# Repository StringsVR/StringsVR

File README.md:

# Strings VR

## Vision

### Overview
StringsVR is aimed to make a wireless SteamVR-compatible setup using the Orange Pi 2W, 6dof tracking also supported through cameras on front of Headset.

### Streaming
StringsVR is currently capable of streaming 2k@72hz over a strong wifi connection with 19ms of latency.
**(This will highly depend on your Wi-Fi it is recommended to have your PC connected to ethernet)** 

### Hardware

#### Power PCB

| Components  | Amount |
| ------------- | ------------- |
| 3200mah 18650 | 3x |
| 18650 Holder PCB | 3x |
| TP4056 | 1x |
| MT3086 | 1x |
| 2x1 Arduino Header | 1x |
| SPDT Power Switch | 1x |
| StringsVR Power PCB | 1x |
| MPU9250 | 1x |

#### Misc
| Components  | Amount |
| ------------- | ------------- |
| Orange Pi Zero 2W 2GB | 1x |
| LS055R1SX04 | 1x |
| HDMI Mini to HDMI Micro USB | 1x |
| USB-Micro USB 5V@1A | 1x |
| 50mmX30mm lenses | 1x |

### Progress ##
**V2 currently is out**, Wiki is not finished but is buildable. V2 will be alot easier setup involving controllers aswell asmore compact

### How To Setup & Build
Check The [Wiki](https://github.com/StringsVR/StringsVR/wiki/Getting-Started).

### Trello & Discord
Trello: https://trello.com/b/QIIqky8U (Add Suggestions to suggestions category)
Discord: stringsbutanalt 

# Project is back in development!!

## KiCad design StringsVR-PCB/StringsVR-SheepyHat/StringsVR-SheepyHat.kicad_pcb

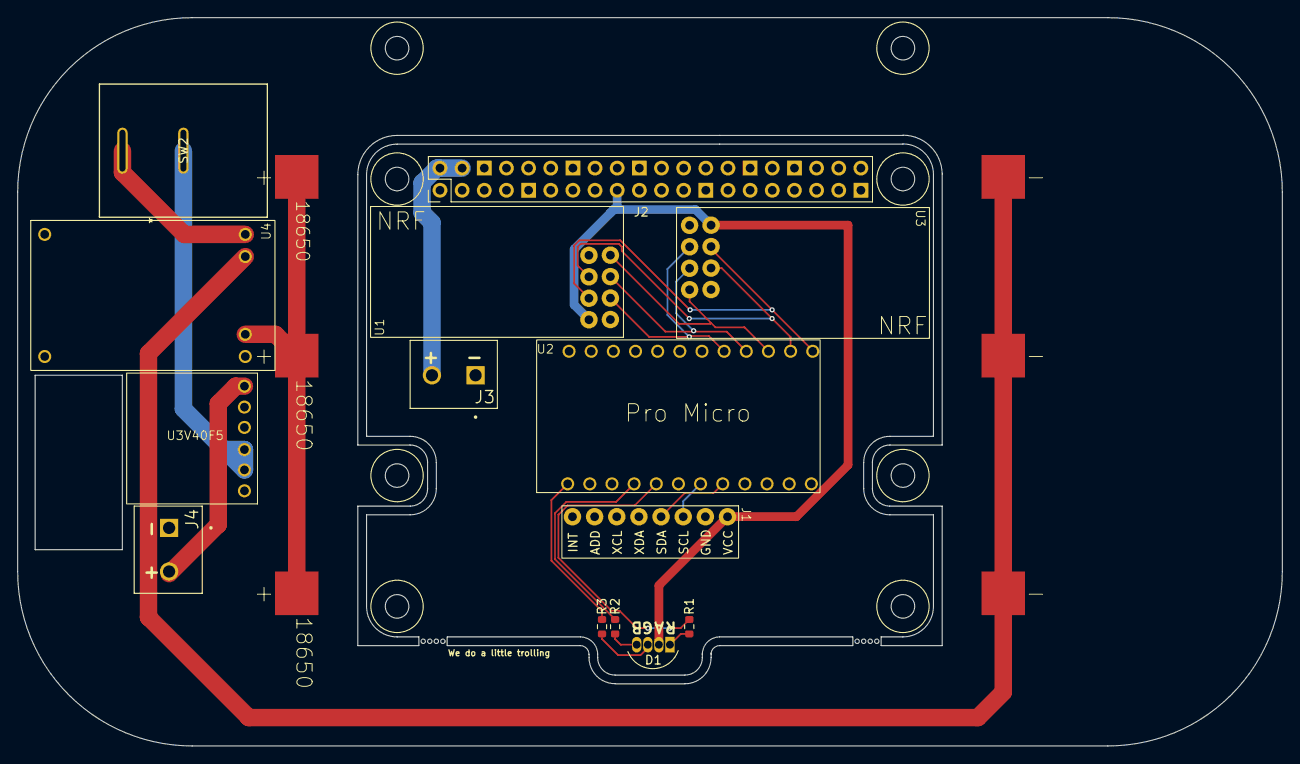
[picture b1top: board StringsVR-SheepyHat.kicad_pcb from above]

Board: 2 copper layers, 145.0 x 83.5 mm, 17 parts (0 on the bottom side), 20 nets.

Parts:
D1: LED_RABG; LED_D5.0mm-4_RGB
J1: MPU6050
J2: Conn_02x20_Odd_Even; Pin_Header_Straight_2x20_Pitch2.54mm
J3, J4: Screw_Terminal_01x02; CUI_TB003-500-P02BE
R1, R2, R3: 220; R_0603_1608Metric
SW2: SRB22A2BBBNN; SW_SRB22A2BBBNN_ZFE
U1, U3: nRF24L01
U2: Pro Micro
U4: TP4056
U5: U3V40F5
U6, U7, U8: 18650SMD

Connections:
5V regulated: J2.2, J2.4, J3.2, J4.2, U5.6 (VOUT)
+3.3V: D1.2 (A), J1.1, J2.17, U1.5 (VCC), U3.5 (VCC)
/B+: U4.4 (B+), U6.1 (b+), U7.1 (b+), U8.1 (b+)
/B-: U4.5 (B-), U6.2 (b-), U7.2 (b-), U8.2 (b-)
CE: U1.2 (CE), U2.20 (Analog), U3.2 (CE)
CSN: U1.6 (CSN), U2.24 (Analog), U3.6 (CSN)
GND: J1.2, J2.6, J2.9, J2.25, J2.30, J2.34, J2.39, J3.1, J4.1, U1.1 (GND), U3.1 (GND), U4.6 (OUT-), U5.4 (GND), U5.5 (GND)
LED_B: R3.2, U2.12 (Analog)
LED_G: R2.2, U2.9 (Analog)
LED_R: R1.2, U2.8 (Analog)
MISO: U1.4 (MISO), U2.22 (MISO), U3.4 (MISO)
MOSI: U1.7 (MOSI), U2.23 (MOSI), U3.7 (MOSI)
unnamed: D1.3 (BK), R3.1
unnamed: D1.4 (GK), R2.1
unnamed: D1.1 (RK), R1.1
unnamed: SW2.2, U5.2 (VIN), U5.3 (VIN)
unnamed: SW2.1, U4.3 (OUT+)
SCK: U1.3 (SCK), U2.21 (SCLK), U3.3 (SCK)
SCL: J1.3, U2.6 (SCL)
SDA: J1.4, U2.5 (SDA)

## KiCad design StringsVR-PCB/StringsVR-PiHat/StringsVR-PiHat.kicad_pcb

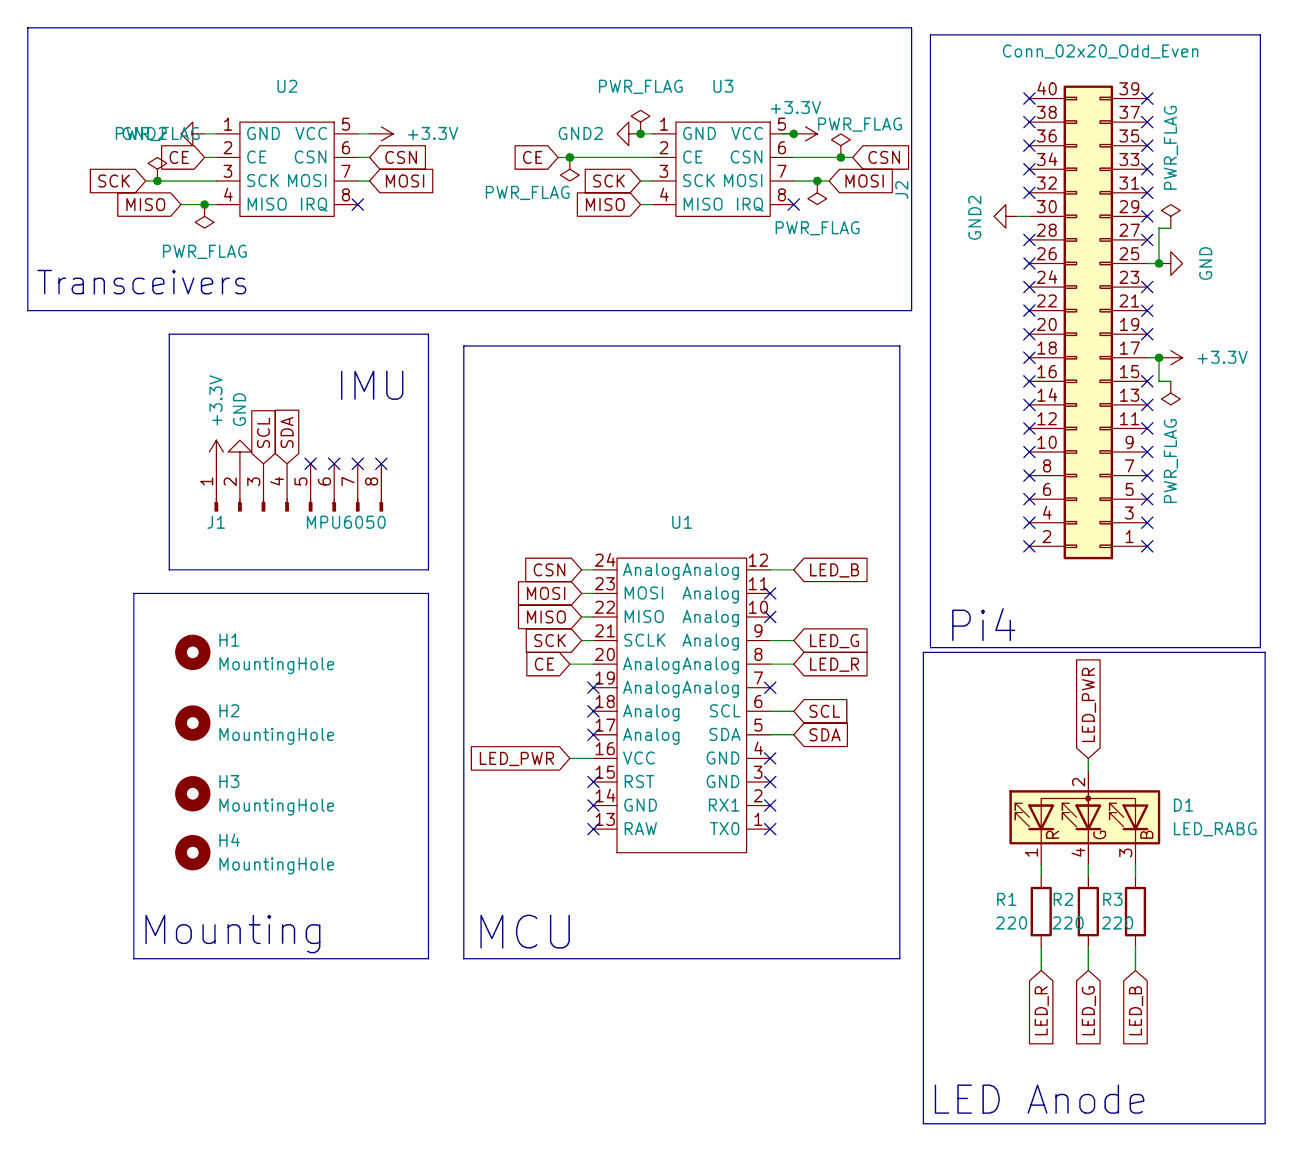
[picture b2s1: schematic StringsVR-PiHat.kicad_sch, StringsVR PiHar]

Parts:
D1: LED_RABG; LED_D5.0mm-4_RGB
H1, H2, H3, H4: MountingHole; MountingHole_2.7mm
J1: MPU6050
J2: Conn_02x20_Odd_Even; Pin_Header_Straight_2x20_Pitch2.54mm
R1, R2, R3: 220; R_0603_1608Metric
U1: Pro Micro
U2, U3: nRF24L01

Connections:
+3.3V: J1.1, J2.17, U2.5 (VCC), U3.5 (VCC)
CE: U1.20 (Analog), U2.2 (CE), U3.2 (CE)
CSN: U1.24 (Analog), U2.6 (CSN), U3.6 (CSN)
GND: J1.2, J2.25
GND2: J2.30, U2.1 (GND), U3.1 (GND)
LED_B: R3.2, U1.12 (Analog)
LED_G: R2.2, U1.9 (Analog)
LED_PWR: D1.2 (A), U1.16 (VCC)
LED_R: R1.2, U1.8 (Analog)
MISO: U1.22 (MISO), U2.4 (MISO), U3.4 (MISO)
MOSI: U1.23 (MOSI), U2.7 (MOSI), U3.7 (MOSI)
unnamed: D1.3 (BK), R3.1
unnamed: D1.4 (GK), R2.1
unnamed: D1.1 (RK), R1.1
SCK: U1.21 (SCLK), U2.3 (SCK), U3.3 (SCK)
SCL: J1.3, U1.6 (SCL)
SDA: J1.4, U1.5 (SDA)

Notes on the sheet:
MCU
Mounting
Transceivers
IMU
Pi4
LED Anode

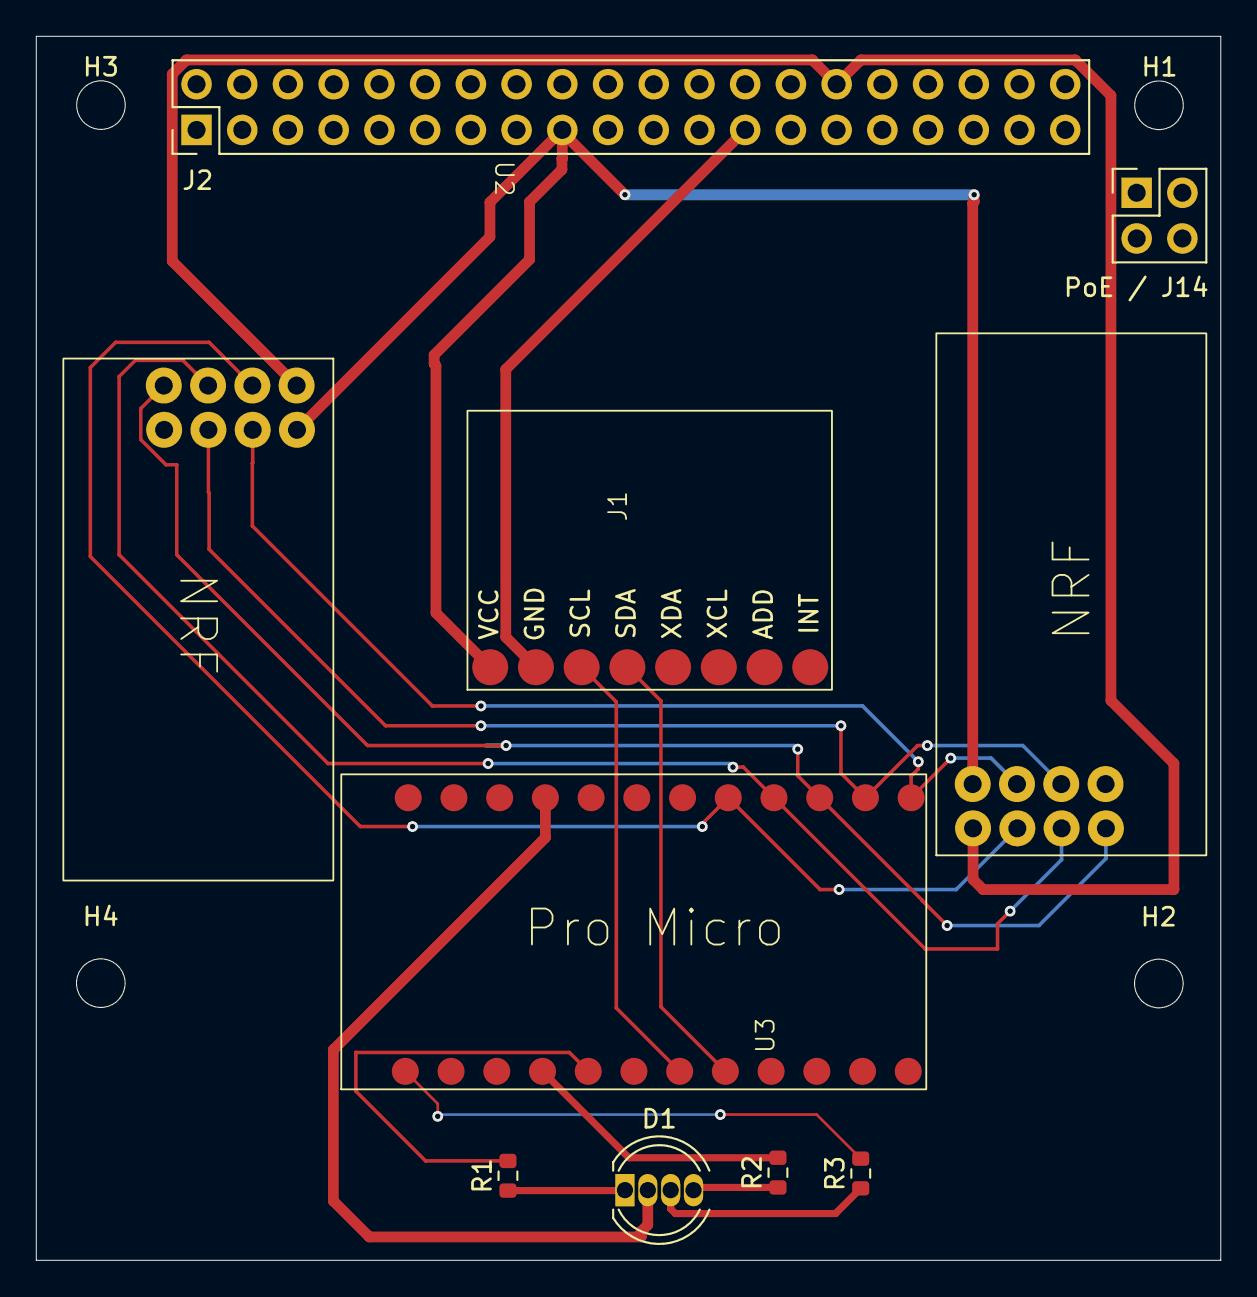
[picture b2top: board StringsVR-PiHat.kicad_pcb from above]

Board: 4 copper layers, 65.8 x 68.0 mm, 14 parts (0 on the bottom side), 17 nets.

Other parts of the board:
PoE / J14: Pin_Header_Straight_2x02_Pitch2.54mm

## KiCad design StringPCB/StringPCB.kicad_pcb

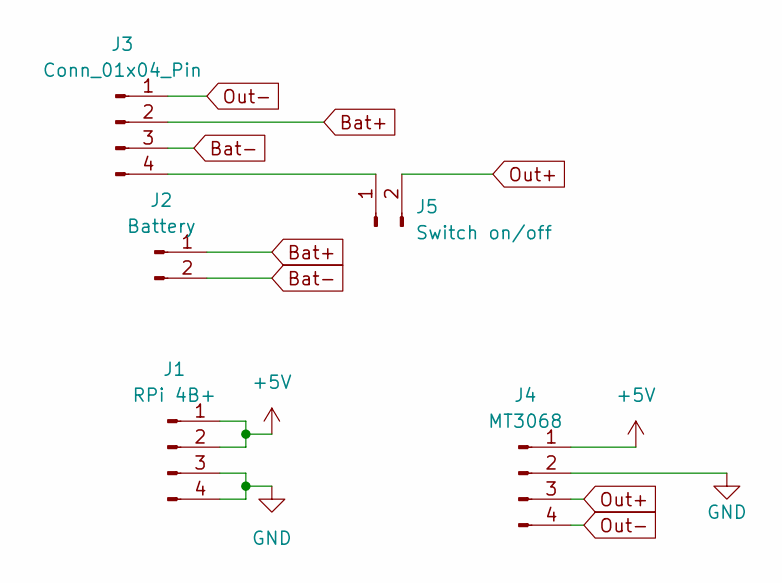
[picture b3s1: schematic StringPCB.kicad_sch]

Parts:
J1: RPi 4B+; PinHeader_1x04_P2.54mm_Vertical
J2: Battery; 18650s 3x
J3: Conn_01x04_Pin; TP4056-module
J4: MT3068
J5: Switch on/off; Fuse_Littelfuse-NANO2-462

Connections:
+5V: J1.1, J1.2, J4.1
Bat+: J2.1, J3.2
Bat-: J2.2, J3.3
GND: J1.3, J1.4, J4.2
unnamed: J3.4, J5.1
Out+: J4.3, J5.2
Out-: J3.1, J4.4

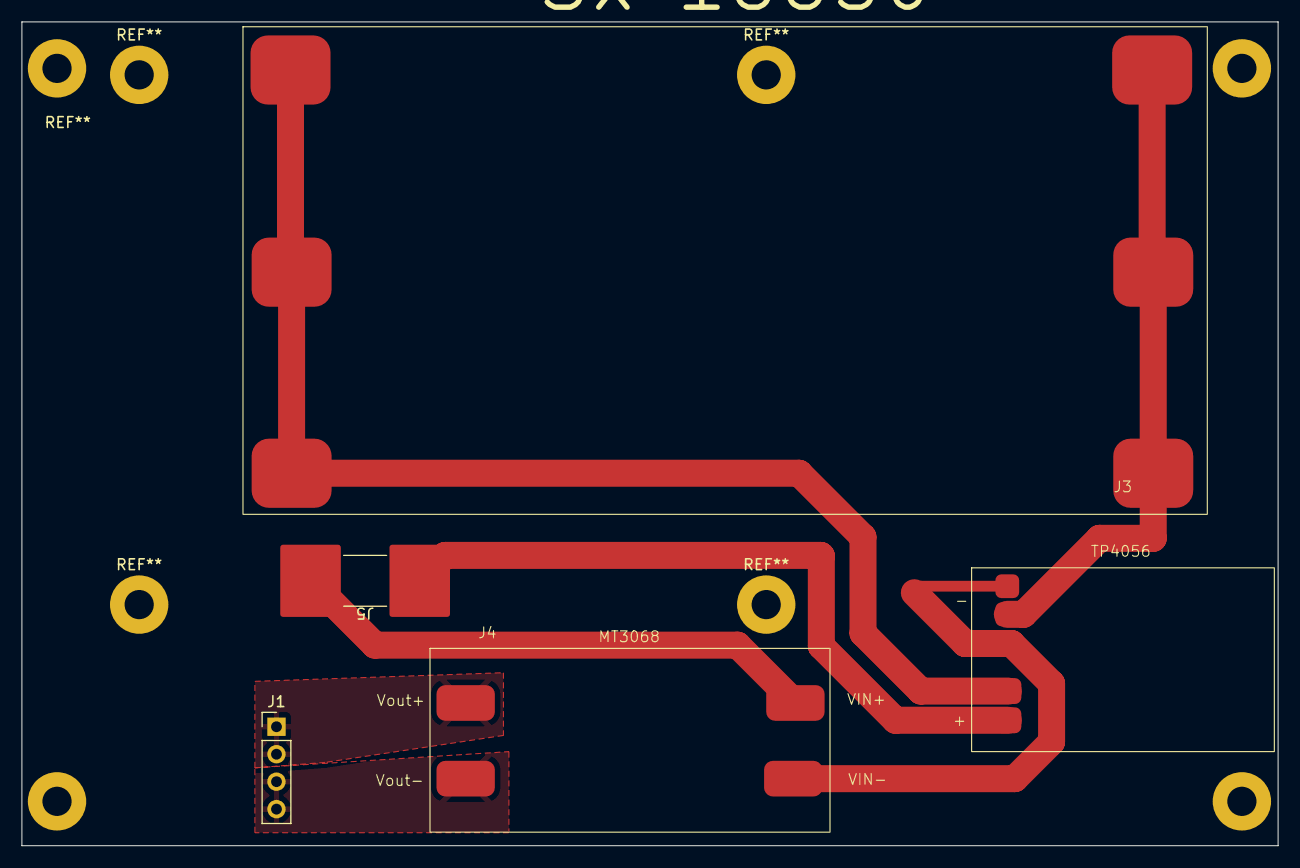
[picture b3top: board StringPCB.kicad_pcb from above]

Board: 2 copper layers, 116.2 x 76.2 mm, 5 parts (0 on the bottom side), 7 nets.

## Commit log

2024-06-06 PCB v1 (Shape Made Be Altered for 3d model)
2024-06-09 Testing HMD. More Support for PCB may be required
2024-06-19 v2 of PCB. Now includes Arduino Boards.
2024-06-21 new integrated board
2024-06-21 moved my changes to separate folder
2024-06-23 added footprints, new pcb
2024-06-23 progress on new pcb
2024-06-24 updated pcb design, new footprints, updated schem a lil
2024-06-24 renamed project so its not just stringsvrpower again
2024-07-10 stuff
2024-07-10 updated schem
